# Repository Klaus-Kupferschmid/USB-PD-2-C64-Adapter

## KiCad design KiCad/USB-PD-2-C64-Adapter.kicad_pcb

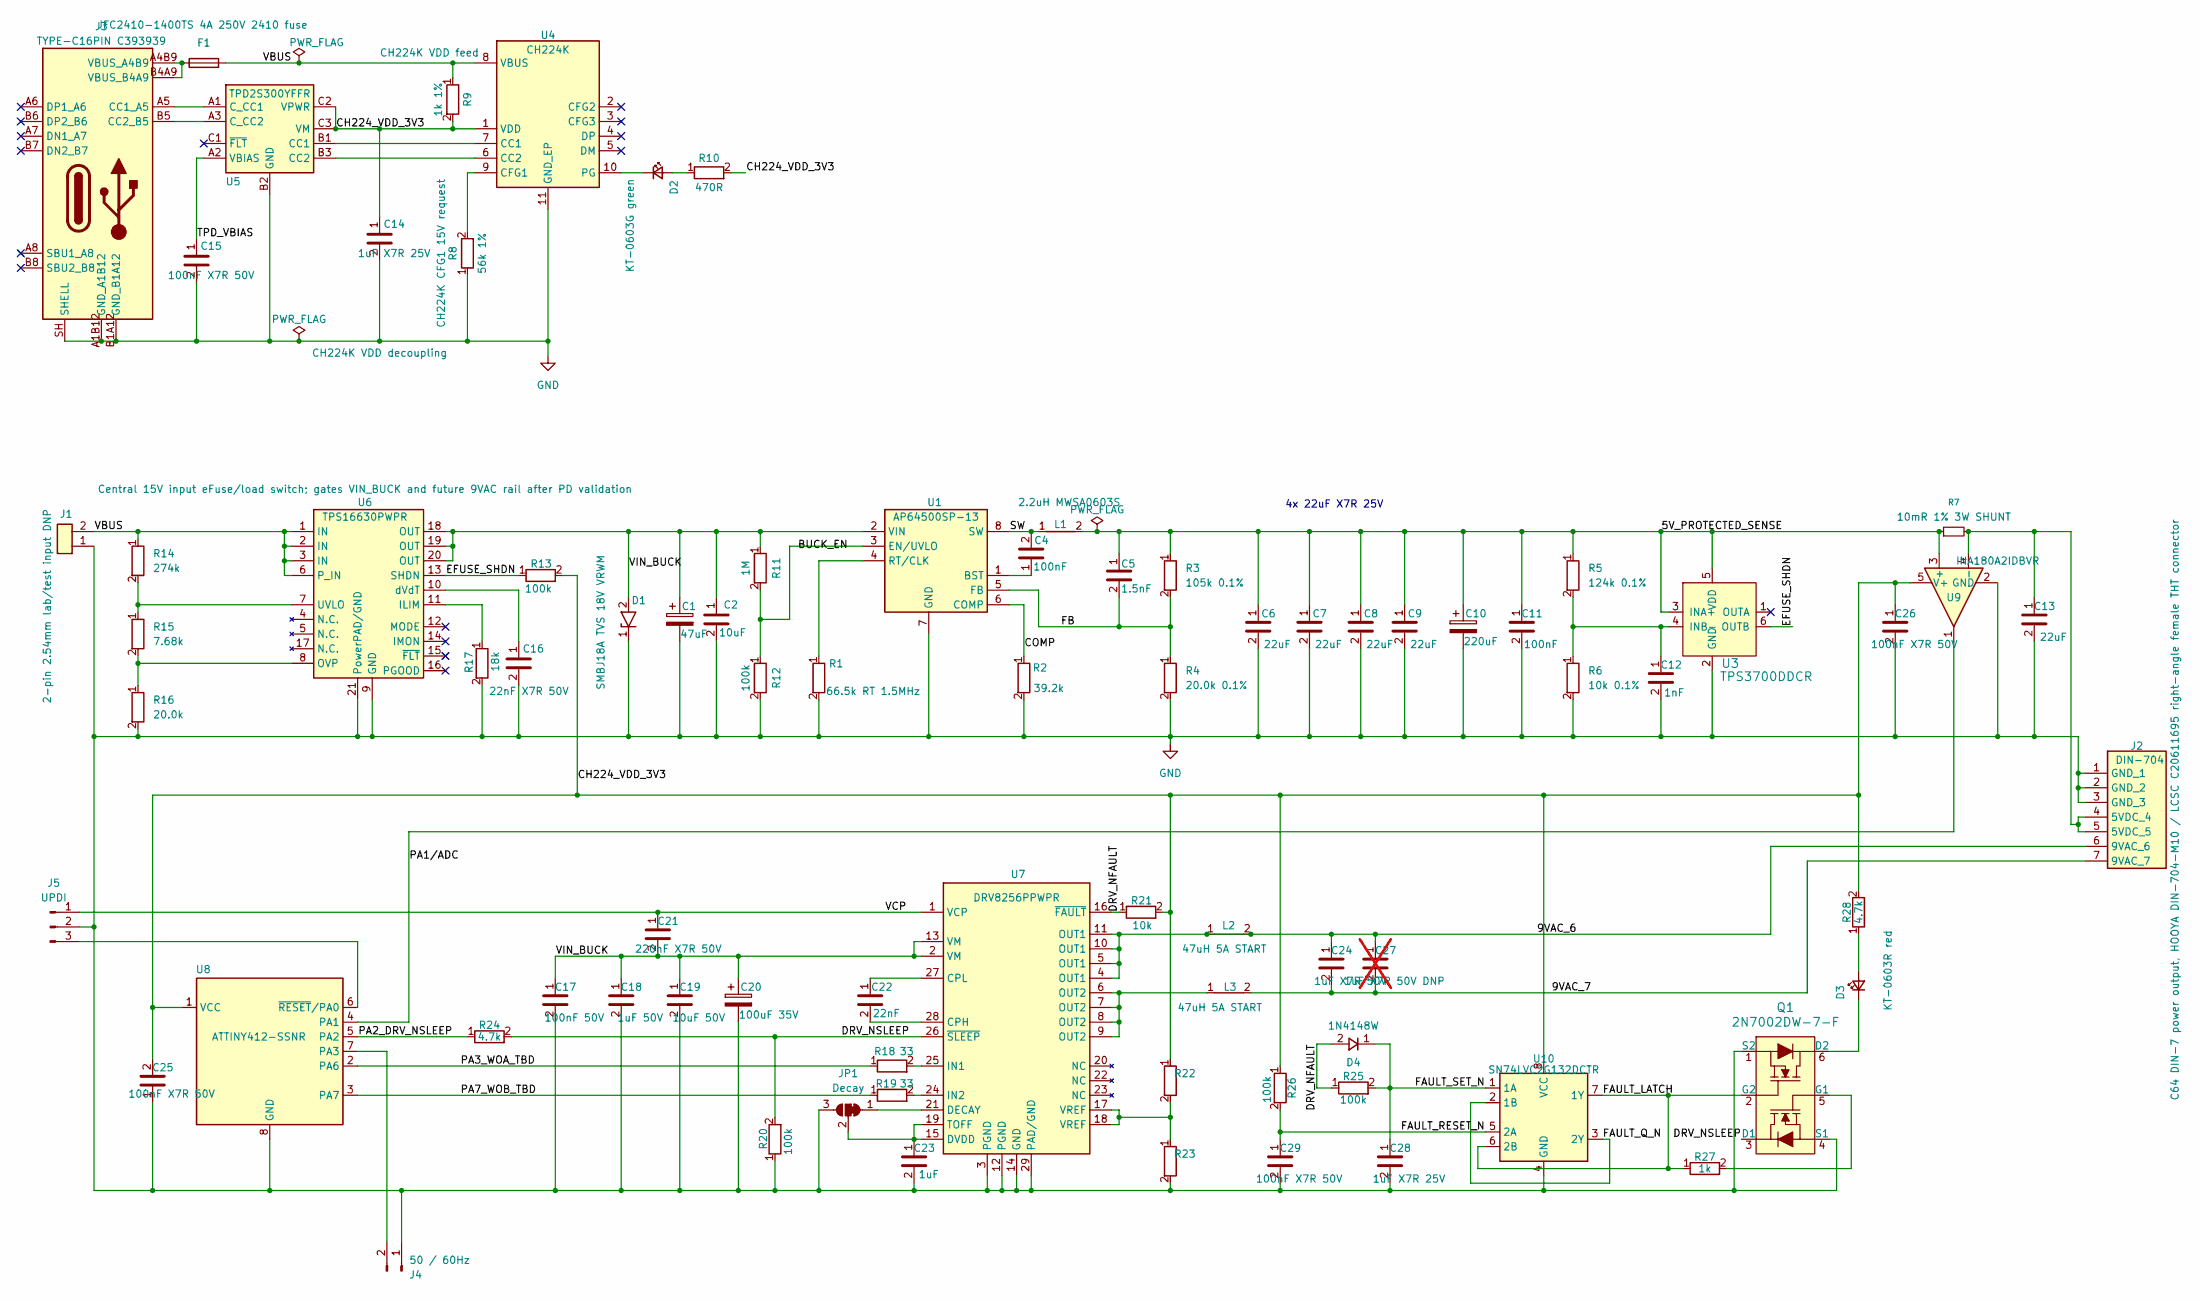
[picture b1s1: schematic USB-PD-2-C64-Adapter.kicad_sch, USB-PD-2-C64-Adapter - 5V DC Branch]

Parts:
C1: 47uF; CP_Elec_6.3x5.8; LCSC C494513
C2: 10uF; C_1210_3225Metric; LCSC C138687
C4, C11: 100nF; C_0603_1608Metric; LCSC C14663
C5: 1.5nF; C_0603_1608Metric; LCSC C710892
C6, C7, C8, C9, C13: 22uF; C_1210_3225Metric; LCSC C2918511
C10: 220uF; CP_Elec_6.3x7.7; LCSC C46550461
C12: 1nF; C_0603_1608Metric; LCSC C507408
C14, C28: 1uF X7R 25V; C_0603_1608Metric; LCSC C29936
C15, C25, C26, C29: 100nF X7R 50V; C_0603_1608Metric; LCSC C14663
C16: 22nF X7R 50V; C_0603_1608Metric; LCSC C106222
C17: 100nF 50V; C_0603_1608Metric; LCSC C14663
C18: 1uF 50V; C_0805_2012Metric; LCSC C28323
C19: 10uF 50V; C_1210_3225Metric; LCSC C138687
C20: 100uF 35V; CP_Elec_6.3x7.7; LCSC C19270709
C21: 220nF X7R 50V; C_0603_1608Metric; LCSC C237192
C22: 22nF; C_0603_1608Metric; LCSC C106222
C23: 1uF; C_0603_1608Metric; LCSC C29936
C24: 1uF X7R 50V; C_1210_3225Metric; LCSC C445699
C27: 1uF X7R 50V DNP; C_1210_3225Metric; LCSC C445699; not fitted
D1: SMBJ18A TVS 18V VRWM; D_SMB; LCSC C353379
D2: KT-0603G green; KT-0603G_C12624; LCSC C12624
D3: KT-0603R red; LED_0603_1608Metric; LCSC C2286
D4: 1N4148W; D_SOD-123; LCSC C81598
F1: JFC2410-1400TS 4A 250V 2410 fuse; XFCN_XF-155_2410_FuseHolder; LCSC C136386
J1: 2-pin 2.54mm lab/test input DNP; PinHeader_1x02_P2.54mm_Vertical; LCSC DNP
J2: DIN-704; DIN-704-M10_C20611695; LCSC C20611695
J3: TYPE-C16PIN C393939; TYPE-C16PIN_C393939; LCSC C393939
J4: 50 / 60Hz; PinHeader_1x02_P2.54mm_Vertical; LCSC DNP
J5: UPDI; PinHeader_1x03_P2.54mm_Vertical; LCSC DNP
JP1: Decay; SolderJumper-3_P1.3mm_Bridged12_RoundedPad1.0x1.5mm; LCSC DNP
L1: 2.2uH MWSA0603S; L_Sunlord_MWSA0603S; LCSC C408445
L2, L3: 47uH 5A START; L_10.4x10.4_H4.8; LCSC C7529419
Q1: 2N7002DW-7-F; SOT-363; MPN 2N7002DW-7-F; Digi-Key_PN 2N7002DW-FDICT-ND
R1: 66.5k RT 1.5MHz; R_0603_1608Metric; LCSC C218113
R2: 39.2k; R_0603_1608Metric; LCSC C217999
R3: 105k 0.1%; R_0603_1608Metric; LCSC C667149
R4: 20.0k 0.1%; R_0603_1608Metric; LCSC C844676
R5: 124k 0.1%; R_0603_1608Metric; LCSC C861097
R6: 10k 0.1%; R_0603_1608Metric; LCSC C844890
R7: 10mR 1% 3W SHUNT; R_2512_6332Metric; LCSC C5375464
R8: 56k 1%; R_0603_1608Metric; LCSC C114630
R9: 1k 1%; R_1206_3216Metric; LCSC C131398
R10: 470R; R_0603_1608Metric; LCSC C23179
R11: 1M; R_0603_1608Metric; LCSC C14675
R12, R13, R20, R25, R26: 100k; R_0603_1608Metric; LCSC C14675
R14: 274k; R_0603_1608Metric; LCSC C482818
R15: 7.68k; R_0603_1608Metric; LCSC C163419
R16: 20.0k; R_0603_1608Metric; LCSC C844676
R17: 18k; R_0603_1608Metric; LCSC C114610
R18, R19: 33; R_0603_1608Metric; LCSC C23140
R21: 10k; R_0603_1608Metric; LCSC C844890
R22, R23: 10k 1%; R_0603_1608Metric; LCSC C844890
R24, R28: 4.7k; R_0603_1608Metric; LCSC C23162
R27: 1k; R_0603_1608Metric; LCSC C21190
U1: AP64500SP-13; SOIC-8-1EP_3.9x4.9mm_P1.27mm_EP2.62x3.51mm_ThermalVias; LCSC C2070920
U3: TPS3700DDCR; SOT-23-6; MPN TPS3700DDCR; Digi-Key_PN 296-30395-1-ND
U4: CH224K; CH224K_ESSOP-10-150mil-1mm; LCSC C970725
U5: TPD2S300YFFR; TPD2S300YFFR_DSBGA-9; LCSC C2650411
U6: TPS16630PWPR; HTSSOP-20-1EP_4.4x6.5mm_P0.65mm_EP3.0x4.2mm; LCSC C1849461
U7: DRV8256PPWPR; Texas_PWP0028V_TSSOP-28-1EP_4.4x9.7mm_P0.65mm_EP3.4x9.7mm_M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; LCSC C3681352
U8: ATTINY412-SSNR; SOIC-8_3.9x4.9mm_P1.27mm; LCSC C1337190
U9: INA180A2IDBVR; SOT-23-5; LCSC C192764
U10: SN74LVC2G132DCTR; VSSOP-8_3x3mm_P0.65mm; LCSC C2870897

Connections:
/5V_PROTECTED_SENSE: C5.1, C6.1, C7.1, C8.1, C9.1, C10.1, C11.1, L1.2, R3.1, R5.1, R7.1, U3.3 (INA+), U3.5 (VDD), U9.3 (+)
/9VAC_6: C24.1, C27.1, J2.6 (9VAC_6), L2.1, L2.2, U7.4 (OUT1), U7.5 (OUT1), U7.10 (OUT1), U7.11 (OUT1)
/9VAC_7: C24.2, C27.2, J2.7 (9VAC_7), L3.2
/BUCK_EN: R11.2, R12.1, U1.3 (EN/UVLO)
/CH224_VDD_3V3: C14.1, C25.2, C26.1, R9.2, R10.2, R13.2, R21.2, R22.1, R26.1, R28.2, U4.1 (VDD), U5.C2 (VPWR), U5.C3 (VM), U8.1 (VCC), U9.5 (V+), U10.8 (VCC)
/COMP: R2.1, U1.6 (COMP)
/DRV_NFAULT: D4.2 (A), R21.1, R25.1, U7.16 (~FAULT)
/DRV_NSLEEP: Q1.3 (D1), R20.2, R24.2, U7.26 (~SLEEP)
/EFUSE_SHDN: R13.1, U3.6 (OUTB), U6.13 (SHDN)
/FAULT_LATCH: Q1.2 (G2), R27.1, U10.6 (2B), U10.7 (1Y)
/FAULT_Q_N: U10.2 (1B), U10.3 (2Y)
/FAULT_RESET_N: C29.1, R26.2, U10.5 (2A)
/FAULT_SET_N: C28.1, D4.1 (K), R25.2, U10.1 (1A)
/FB: C5.2, R3.2, R4.1, U1.5 (FB)
/PA1/ADC: U8.4 (PA1), U9.1
/PA2_DRV_NSLEEP: R24.1, U8.5 (PA2)
/PA3_WOA_TBD: R18.1, U8.2 (PA6)
/PA7_WOB_TBD: R19.1, U8.3 (PA7)
/SW: C4.2, L1.1, U1.8 (SW)
/TPD_VBIAS: C15.1, U5.A2 (VBIAS)
/VBUS: F1.2, J1.2, R9.1, R14.1, U4.8 (VBUS), U6.1 (IN), U6.2 (IN), U6.3 (IN), U6.6 (P_IN)
/VCP: C21.1, J5.1, U7.1 (VCP)
/VIN_BUCK: C1.1, C2.1, C17.1, C18.1, C19.1, C20.1, C21.2, D1.2 (A2), R11.1, U1.2 (VIN), U6.18 (OUT), U6.19 (OUT), U6.20 (OUT), U7.2 (VM), U7.13 (VM)
GND: C1.2, C2.2, C6.2, C7.2, C8.2, C9.2, C10.2, C11.2, C12.2, C13.2, C14.2, C15.2, C16.2, C17.2, C18.2, C19.2, C20.2, C23.2, C25.1, C26.2, C28.2, C29.2, D1.1 (A1), J1.1, J2.1 (GND_1), J2.2 (GND_2), J2.3 (GND_3), J3.A1B12 (GND_A1B12), J3.B1A12 (GND_B1A12), J3.SH (SHELL), J4.1, J5.2, JP1.3 (B), Q1.1 (S2), Q1.4 (S1), R1.2, R2.2, R4.2, R6.2, R8.1, R12.2, R16.2, R17.2, R20.1, R23.2, U1.7 (GND), U3.2 (GND), U4.11 (GND_EP), U5.B2 (GND), U6.9 (GND), U6.21 (PowerPAD/GND), U7.3 (PGND), U7.12 (PGND), U7.14 (GND), U7.29 (PAD/GND), U8.8 (GND), U9.2 (GND), U10.4 (GND)
unnamed: D2.2 (A), R10.1
unnamed: D2.1 (K), U4.10 (PG)
unnamed: D3.2 (A), R28.1
unnamed: D3.1 (K), Q1.6 (D2)
unnamed: C13.1, J2.4 (5VDC_4), J2.5 (5VDC_5), R7.2, U9.4 (-)
unnamed: J3.A5 (CC1_A5), U5.A1 (C_CC1)
unnamed: J3.B5 (CC2_B5), U5.A3 (C_CC2)
unnamed: F1.1, J3.A4B9 (VBUS_A4B9), J3.B4A9 (VBUS_B4A9)
unnamed: J4.2, U8.7 (PA3)
unnamed: J5.3, U8.6 (~RESET/PA0)
unnamed: JP1.1 (A), U7.21 (DECAY)
unnamed: C23.1, JP1.2 (C), U7.15 (DVDD), U7.19 (TOFF)
unnamed: L3.1, U7.6 (OUT2), U7.7 (OUT2), U7.8 (OUT2), U7.9 (OUT2)
unnamed: Q1.5 (G1), R27.2
unnamed: R22.2, R23.1, U7.17 (VREF), U7.18 (VREF)
unnamed: C4.1, U1.1 (BST)
unnamed: R1.1, U1.4 (RT/CLK)
unnamed: C12.1, R5.2, R6.1, U3.4 (INB-)
unnamed: U4.7 (CC1), U5.B1 (CC1)
unnamed: U4.6 (CC2), U5.B3 (CC2)
unnamed: R8.2, U4.9 (CFG1)
unnamed: R17.1, U6.11 (ILIM)
unnamed: R15.2, R16.1, U6.8 (OVP)
unnamed: R14.2, R15.1, U6.7 (UVLO)
unnamed: C16.1, U6.10 (dVdT)
unnamed: C22.2, U7.28 (CPH)
unnamed: C22.1, U7.27 (CPL)
unnamed: R18.2, U7.25 (IN1)
unnamed: R19.2, U7.24 (IN2)

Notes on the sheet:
4x 22uF X7R 25V

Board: 2 copper layers, 79 parts (0 on the bottom side), 50 nets, no tracks yet.

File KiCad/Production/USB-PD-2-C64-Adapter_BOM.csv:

Designator,Comment,Footprint,LCSC Part Number,Quantity,Baugruppe
J3,SHOU HAN TYPE-C16PIN USB-C receptacle 16P 30V 3A,USB-PD-2-C64-Adapter:TYPE-C16PIN_C393939,C393939,1,USB-PD Eingang
U4,CH224K USB PD sink controller 15V request,USB-PD-2-C64-Adapter:CH224K_ESSOP-10-150mil-1mm,C970725,1,USB-PD Eingang
U5,TPD2S300YFFR USB-C CC short-to-VBUS and IEC ESD protector,USB-PD-2-C64-Adapter:TPD2S300YFFR_DSBGA-9,C2650411,1,USB-PD Eingang
U6,TPS16630PWPR central 15V input eFuse/load switch HTSSOP-20,Package_SO:HTSSOP-20-1EP_4.4x6.5mm_P0.65mm_EP3.0x4.2mm,C1849461,1,USB-PD Eingang
C16,22nF X7R 50V U6 dVdT soft-start capacitor start value,Capacitor_SMD:C_0603_1608Metric,C106222,1,USB-PD Eingang
R8,56k 1% CH224K CFG1 15V request,Resistor_SMD:R_0603_1608Metric,C114630,1,USB-PD Eingang
R9,1k 1% CH224K VDD feed 1206,Resistor_SMD:R_1206_3216Metric,C131398,1,USB-PD Eingang
R10,470R 1% 15V PG LED resistor,Resistor_SMD:R_0603_1608Metric,C23179,1,USB-PD Eingang
R11,1M 1% AP64500 EN/UVLO top start value,Resistor_SMD:R_0603_1608Metric,C105578,1,USB-PD Eingang
R12,100k 1% AP64500 EN/UVLO bottom start value,Resistor_SMD:R_0603_1608Metric,C14675,1,USB-PD Eingang
R13,100k 1% U6 SHDN pull-up to CH224_VDD,Resistor_SMD:R_0603_1608Metric,C14675,1,USB-PD Eingang
R14,274k 1% U6 UVLO/OVP divider top start value,Resistor_SMD:R_0603_1608Metric,C482818,1,USB-PD Eingang
R15,7.68k 1% U6 UVLO/OVP divider middle start value,Resistor_SMD:R_0603_1608Metric,C163419,1,USB-PD Eingang
R16,20.0k 1% U6 UVLO/OVP divider bottom start value,Resistor_SMD:R_0603_1608Metric,C844676,1,USB-PD Eingang
R17,18k 1% U6 ILIM resistor start value,Resistor_SMD:R_0603_1608Metric,C114610,1,USB-PD Eingang
C14,1uF X7R 25V CH224K VDD decoupling,Capacitor_SMD:C_0603_1608Metric,C29936,1,USB-PD Eingang
C15,100nF X7R 50V TPD2S300 VBIAS support capacitor,Capacitor_SMD:C_0603_1608Metric,C14663,1,USB-PD Eingang
D2,KT-0603G emerald green 0603 15V PD status LED,USB-PD-2-C64-Adapter:KT-0603G_C12624,C12624,1,USB-PD Eingang
J1,2-pin 2.54mm lab/test input header DNP not normally populated,Connector_PinHeader_2.54mm:PinHeader_1x02_P2.54mm_Vertical,DNP,1,USB-PD Eingang
D1,SMBJ18A TVS 18V VRWM,Diode_SMD:D_SMB,C353379,1,USB-PD Eingang
F1,JFC2410-1400TS 4A 250V 2410 fuse,USB-PD-2-C64-Adapter:XFCN_XF-155_2410_FuseHolder,C136386,1,USB-PD Eingang
FH1,XFCN XF-155 2410/6125 SMD fuse holder (holds F1),USB-PD-2-C64-Adapter:XFCN_XF-155_2410_FuseHolder,C41371860,1,USB-PD Eingang
C1,47uF polymer input bulk,Capacitor_SMD:CP_Elec_6.3x5.8,C494513,1,USB-PD Eingang
"C2,C3",10uF X7R input MLCC,Capacitor_SMD:C_1210_3225Metric,C138687,2,USB-PD Eingang
C4,100nF BST-SW bootstrap,Capacitor_SMD:C_0603_1608Metric,C14663,1,5VDC
C5,1.5nF compensation,Capacitor_SMD:C_0603_1608Metric,C710892,1,5VDC
"C6,C7,C8,C9,C13",22uF X7R output MLCC,Capacitor_SMD:C_1210_3225Metric,C2918511,5,5VDC
C10,220uF polymer output bulk,Capacitor_SMD:CP_Elec_6.3x7.7,C46550461,1,5VDC
C11,100nF,Capacitor_SMD:C_0603_1608Metric,C14663,1,5VDC
C12,1nF,Capacitor_SMD:C_0603_1608Metric,C507408,1,5VDC
L1,2.2uH MWSA0603S Isat 10A IRMS 9.5A DCR 15mR,Inductor_SMD:L_Sunlord_MWSA0603S,C408445,1,5VDC
R1,66.5k RT 1.5MHz,Resistor_SMD:R_0603_1608Metric,C218113,1,5VDC
R2,39.2k,Resistor_SMD:R_0603_1608Metric,C217999,1,5VDC
R3,105k 0.1%,Resistor_SMD:R_0603_1608Metric,C667149,1,5VDC
R4,20.0k 0.1%,Resistor_SMD:R_0603_1608Metric,C844676,1,5VDC
R5,124k 0.1%,Resistor_SMD:R_0603_1608Metric,C861097,1,5VDC
R6,10k 0.1%,Resistor_SMD:R_0603_1608Metric,C844890,1,5VDC
R7,10mR 1% 3W 2512 5V load-sense shunt for INA180A2 Kelvin-near layout,Resistor_SMD:R_2512_6332Metric,C5375464,1,5VDC
U9,INA180A2IDBVR 50V/V high-side current-sense amplifier for 5V load detection,Package_TO_SOT_SMD:SOT-23-5,C192764,1,5VDC
C26,100nF X7R 50V INA180A2 local V+ decoupling,Capacitor_SMD:C_0603_1608Metric,C14663,1,5VDC
U1,AP64500SP-13 synchronous buck 3.8V-40V 5A,USB-PD-2-C64-Adapter:SOIC-8-1EP_3.9x4.9mm_P1.27mm_EP2.62x3.51mm_ThermalVias,C2070920,1,5VDC
U3,TPS3700DDCR window comparator OVP SOT-23-6,Package_TO_SOT_SMD:SOT-23-6,C33002,1,5VDC
J2,HOOYA DIN-704-M10 C64 DIN-7 power out 1 GND_1 2 GND_2 3 GND_3 4 5VDC_4 5 5VDC_5 6 9VAC_6 7 9VAC_7,USB-PD-2-C64-Adapter:DIN-704-M10_C20611695,C20611695,1,5VDC
U7,DRV8256PPWPR differential 9VAC H-bridge driver from VIN_BUCK,Package_SO:Texas_PWP0028V_TSSOP-28-1EP_4.4x9.7mm_P0.65mm_EP3.4x9.7mm_Mask2.94x5.62mm_ThermalVias,C3681352,1,9VAC
U8,ATTINY412-SSNR 9VAC sine PWM and load-detect controller,Package_SO:SOIC-8_3.9x4.9mm_P1.27mm,C1337190,1,9VAC
C17,100nF 50V DRV8256 VM local ceramic decoupling,Capacitor_SMD:C_0603_1608Metric,C14663,1,9VAC
C18,1uF 50V DRV8256 VM local ceramic decoupling,Capacitor_SMD:C_0805_2012Metric,C28323,1,9VAC
C19,10uF 50V DRV8256 VM input ceramic capacitor,Capacitor_SMD:C_1210_3225Metric,C138687,1,9VAC
C20,100uF 35V DRV8256 local VIN_BUCK bulk capacitor start value,Capacitor_SMD:CP_Elec_6.3x7.7,C19270709,1,9VAC
C21,220nF X7R 50V DRV8256 VCP-to-VM charge pump capacitor,Capacitor_SMD:C_0603_1608Metric,C237192,1,9VAC
C22,22nF X7R 50V DRV8256 CPH-to-CPL charge pump capacitor,Capacitor_SMD:C_0603_1608Metric,C106222,1,9VAC
C23,1uF X7R 25V DRV8256 DVDD regulator decoupling,Capacitor_SMD:C_0603_1608Metric,C29936,1,9VAC
"R18,R19",33R DRV8256 IN1/IN2 series resistors start value,Resistor_SMD:R_0603_1608Metric,C23140,2,9VAC
R20,100k DRV8256 nSLEEP pulldown,Resistor_SMD:R_0603_1608Metric,C14675,1,9VAC
R21,10k DRV8256 nFAULT pull-up,Resistor_SMD:R_0603_1608Metric,C844890,1,9VAC
"R22,R23",10k 1% DRV8256 VREF divider start ITRIP about 3.8A peak,Resistor_SMD:R_0603_1608Metric,C844890,2,9VAC
"L2,L3",47uH 5A 9VAC differential LC output filter inductors start value,Inductor_SMD:L_10.4x10.4_H4.8,C7529419,2,9VAC
C24,1uF X7R 50V differential 9VAC output LC filter capacitor,Capacitor_SMD:C_1210_3225Metric,C445699,1,9VAC
C25,100nF X7R 50V ATtiny412 VCC local decoupling,Capacitor_SMD:C_0603_1608Metric,C14663,1,9VAC
C27,1uF X7R 50V optional parallel differential 9VAC output LC filter capacitor DNP,Capacitor_SMD:C_1210_3225Metric,DNP,1,9VAC
J4,50/60Hz selection 2-pin 2.54mm header DNP,Connector_PinHeader_2.54mm:PinHeader_1x02_P2.54mm_Vertical,DNP,1,9VAC
J5,UPDI programming 3-pin 2.54mm header DNP,Connector_PinHeader_2.54mm:PinHeader_1x03_P2.54mm_Vertical,DNP,1,9VAC
JP1,DRV8256 DECAY solder jumper bridged 1-2 no fitted part,Jumper:SolderJumper-3_P1.3mm_Bridged12_RoundedPad1.0x1.5mm,DNP,1,9VAC
U10,SN74LVC2G132DCTR dual Schmitt NAND used as delayed DRV8256 nFAULT latch,Package_SO:VSSOP-8_3x3mm_P0.65mm,C2870897,1,9VAC
Q1,2N7002DW-7-F dual N-channel MOSFET array for nSLEEP pulldown and fault LED sink,Package_TO_SOT_SMD:SOT-363_SC-70-6,C83571,1,9VAC
D3,KT-0603R red 0603 fault indicator LED,LED_SMD:LED_0603_1608Metric,C2286,1,9VAC
D4,1N4148W SOD-123 nFAULT delay-capacitor fast-recharge diode,Diode_SMD:D_SOD-123,C81598,1,9VAC
"R24,R28",4.7k 1% 0603 PA2 series and fault LED resistors,Resistor_SMD:R_0603_1608Metric,C23162,2,9VAC
"R25,R26",100k 1% 0603 fault delay and reset resistors,Resistor_SMD:R_0603_1608Metric,C14675,2,9VAC
R27,1k 1% 0603 fault latch output gate resistor,Resistor_SMD:R_0603_1608Metric,C21190,1,9VAC
C28,1uF X7R 25V nFAULT delay capacitor,Capacitor_SMD:C_0603_1608Metric,C29936,1,9VAC
C29,100nF X7R 50V fault latch reset capacitor,Capacitor_SMD:C_0603_1608Metric,C14663,1,9VAC

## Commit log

2026-06-04 Initial commit: USB-PD to C64 Power Adapter KiCad project
2026-06-04 Update copilot-instructions with full project spec and add JLCPCB BOM CSV
2026-06-04 Fix 5V tolerance: ±3% (4.85V-5.15V)
2026-06-04 Add C64 power supply best practices checklist
2026-06-22 5V-Zweig fertig: AP64500-Buck, Schutz, 3D-Modelle, BOM/Lib konsolidiert
    - 5V-Strang komplett auf AP64500SP-13 (C2070920) umgestellt, RT6318C entfernt (Symbole/Datasheet/Altdateien geloescht)
    - U1-Footprint korrigiert auf SOIC-8-1EP EP2.62x3.51mm_ThermalVias; Projekt-Library .pretty + .3dshapes angelegt
    - 3D-Modelle fuer U1 (SOIC-8-1EP STEP) und F1 (Littelfuse OMNI-BLOK STEP) eingebunden, PCB direkt gepatcht
    - BOM CSV/TXT, copilot-instructions und KiCad-Symbole konsistent mit Schaltplan; fp-lib-table + Datasheets ergaenzt
2026-06-23 Update USB-PD input protection assets
2026-06-24 Update 9VAC design assets
